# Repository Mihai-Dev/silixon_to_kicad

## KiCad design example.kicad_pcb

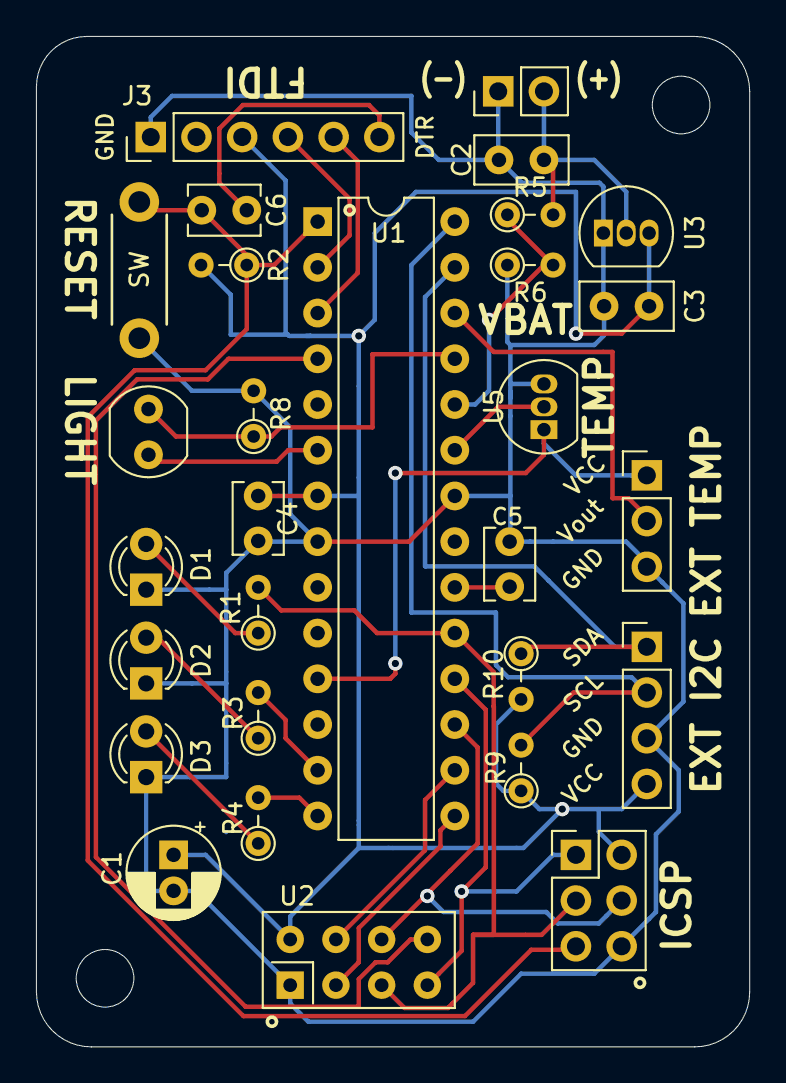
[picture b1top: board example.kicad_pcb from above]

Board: 2 copper layers, 39.6 x 56.1 mm, 29 parts (0 on the bottom side), 27 nets.

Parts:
C1: 10uF 16V; CP_Radial_D5.0mm_P2.00mm
C2, C3: 1uF; C_Disc_D5.0mm_W2.5mm_P2.50mm
C4, C5, C6: 0.1uF; C_Disc_D3.8mm_W2.6mm_P2.50mm
D1: GRN; LED_D3.0mm
D2: YEL; LED_D3.0mm
D3: RED; LED_D3.0mm
J1: 3xAA Battery; PinHeader_1x02_P2.54mm_Vertical
J2: AVR-ISP-6; PinHeader_2x03_P2.54mm_Vertical
J3: FTDI; PinHeader_1x06_P2.54mm_Vertical
J4: BME280 Pinouts; PinHeader_1x04_P2.54mm_Vertical
J5: EXT_TEMP; PinHeader_1x03_P2.54mm_Vertical
R1, R3, R4: 470; R_Axial_DIN0204_L3.6mm_D1.6mm_P2.54mm_Vertical
R2: 10k; R_Axial_DIN0204_L3.6mm_D1.6mm_P2.54mm_Vertical
R5: 330K; R_Axial_DIN0204_L3.6mm_D1.6mm_P2.54mm_Vertical
R6: 100K; R_Axial_DIN0204_L3.6mm_D1.6mm_P2.54mm_Vertical
R7: R_PHOTO; R_LDR_4.9x4.2mm_P2.54mm_Vertical
R8: 4.7K; R_Axial_DIN0204_L3.6mm_D1.6mm_P2.54mm_Vertical
R9, R10: 4.7k; R_Axial_DIN0204_L3.6mm_D1.6mm_P2.54mm_Vertical
SW1: SW_Push; SW_PUSH_L6mm_W3.5mm_H5mm
U1: ATmega328P-PU; DIP-28_W7.62mm
U2: NRF24L01; nRF24L01
U3: MCP1700-3302E_TO92; TO-92_Inline
U5: LM35DZ; TO-92_Inline

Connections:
BAT(+): C2.1, J1.2, R5.2, U3.2
CE: U1.15, U2.3
EXT_TEMPPIN: J5.2, U1.26
Earth: C1.2, C2.2, C3.2, C4.2, C5.1, D1.1, D2.1, D3.1, J1.1, J2.6, J3.1, J4.3, J5.3, R6.1, R8.2, SW1.2, U1.8, U1.22, U2.1, U3.1, U5.3
IRQ: U1.4, U2.8
LIGHTPIN: R7.1, R8.1, U1.25
LIGHTPOWER: R7.2, U1.6
MISO: J2.1, U1.18, U2.7
MOSI: J2.4, U1.17, U2.6
unnamed: C5.2, U1.20
unnamed: C6.1, J3.6
unnamed: D1.2, R1.1
unnamed: D2.2, R3.1
unnamed: D3.2, R4.1
REDLED: R4.2, U1.14
RESET: C6.2, J2.5, R2.1, SW1.1, U1.1
RXD: J3.4, U1.2
SCK: J2.3, R1.2, U1.19, U2.5
SCL: J4.2, R9.2, U1.28
SDA: J4.1, R10.1, U1.27
TEMPPIN: U1.23, U5.2
TEMPPOWER: J5.1, U1.11, U5.1
TXD: J3.5, U1.3
VBAT: R5.1, R6.2, U1.24
VCC1: C1.1, C3.1, C4.1, J2.2, J3.3, J4.4, R2.2, R9.1, R10.2, U1.7, U2.2, U3.3
YELLED: R3.2, U1.13
~CSN: U1.16, U2.4

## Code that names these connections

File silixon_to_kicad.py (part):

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        (net (code 3) (name LIGHTPOWER)
        (node (ref U1) (pin 6))
        (node (ref R7) (pin 2)))
        (net (code 4) (name LIGHTPIN)
        (node (ref R7) (pin 1))
        (node (ref R8) (pin 1))
        (node (ref U1) (pin 25)))
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        (node (ref J5) (pin 1))
        (node (ref U5) (pin 1))
        (node (ref U1) (pin 11)))
        (net (code 19) (name EXT_TEMPPIN)
        (node (ref U1) (pin 26))
        (node (ref J5) (pin 2)))
        (net (code 20) (name IRQ)
        (node (ref U2) (pin 8))
        (node (ref U1) (pin 4)))
        (net (code 21) (name TEMPPIN)
        (node (ref U5) (pin 2))
        (node (ref U1) (pin 23)))
        (net (code 22) (name "Net-(U1-Pad21)")
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
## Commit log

2025-08-10 intial commit
2025-08-10 First iteration of conversion
2025-08-10 Fixed display issue
